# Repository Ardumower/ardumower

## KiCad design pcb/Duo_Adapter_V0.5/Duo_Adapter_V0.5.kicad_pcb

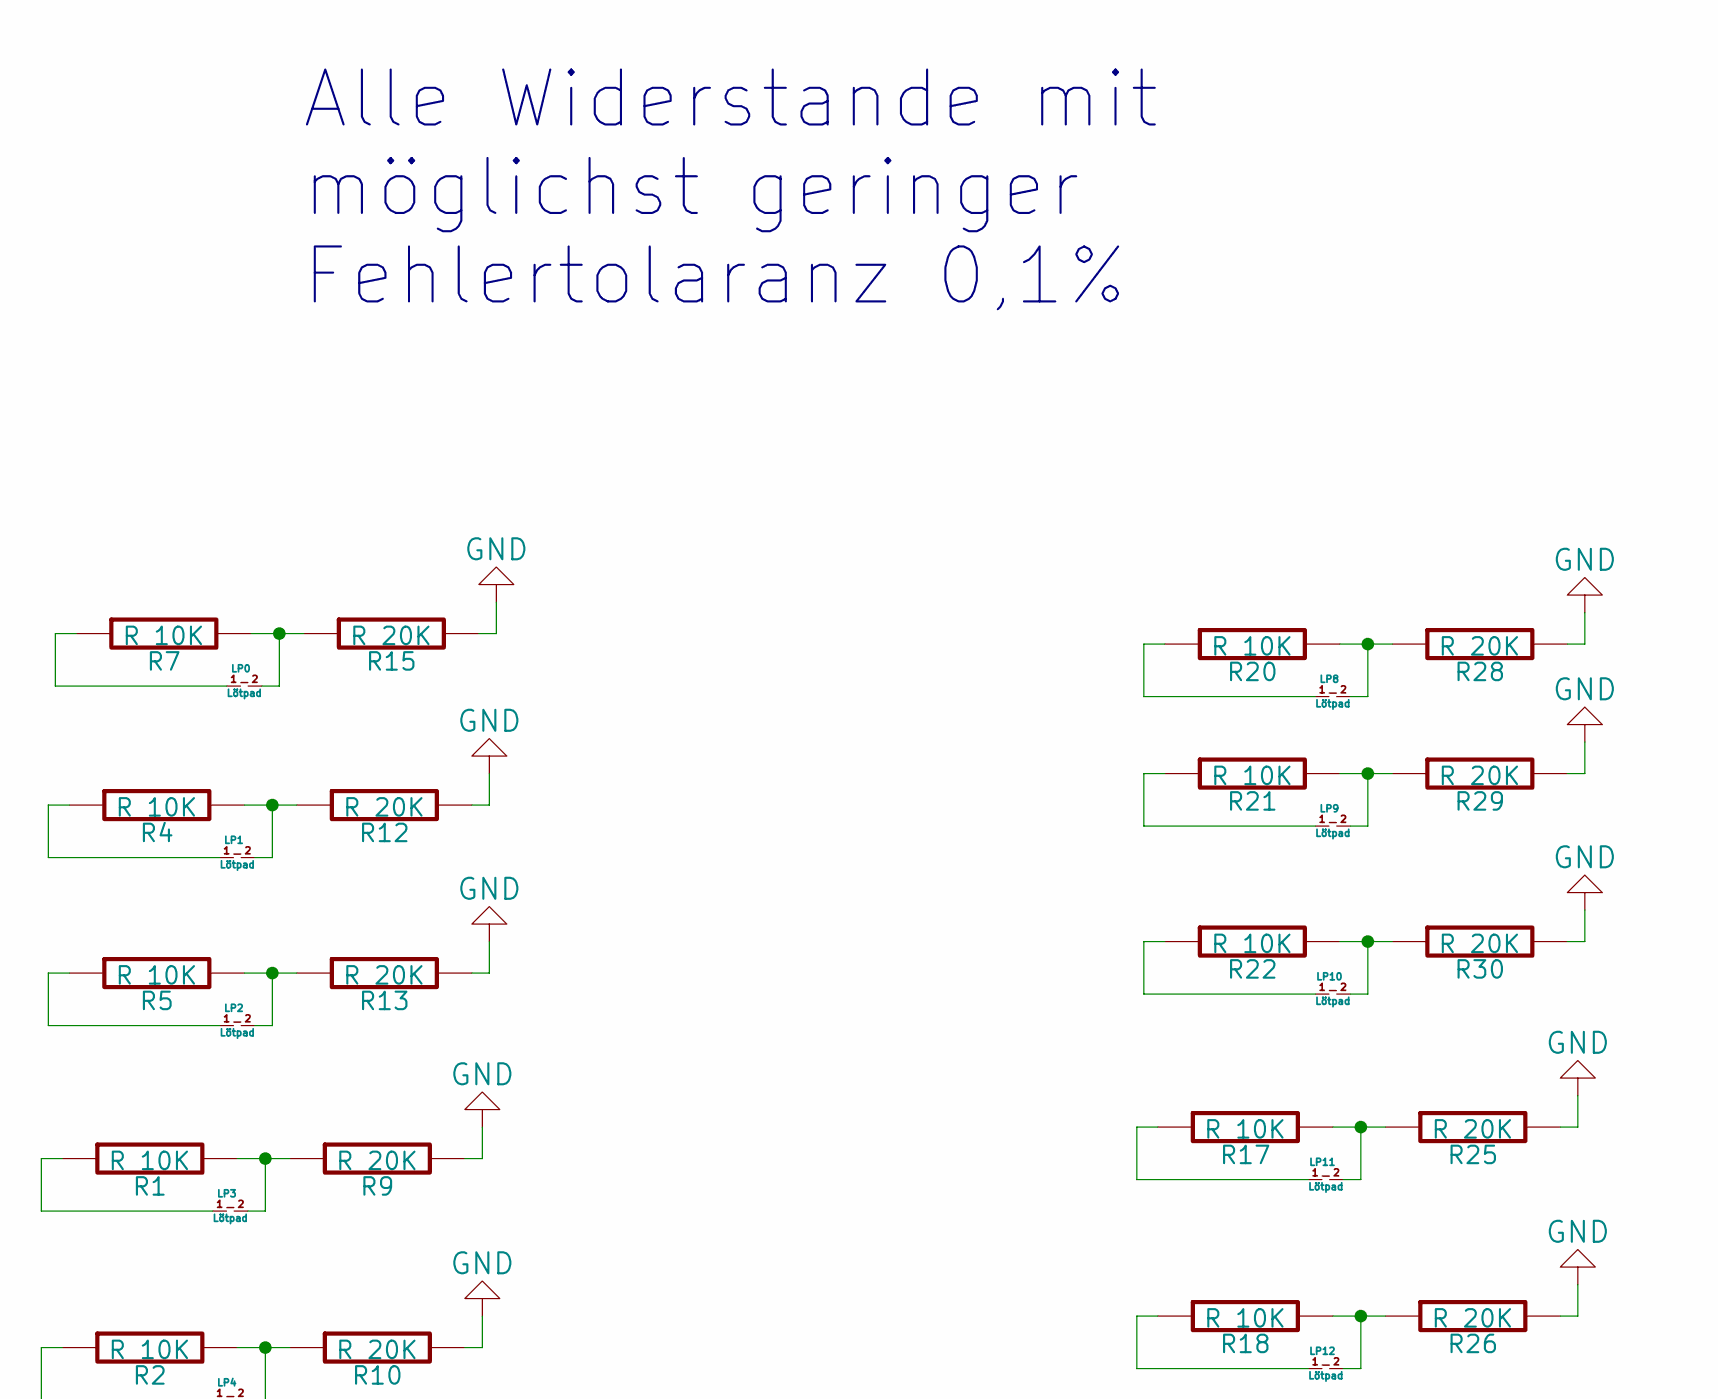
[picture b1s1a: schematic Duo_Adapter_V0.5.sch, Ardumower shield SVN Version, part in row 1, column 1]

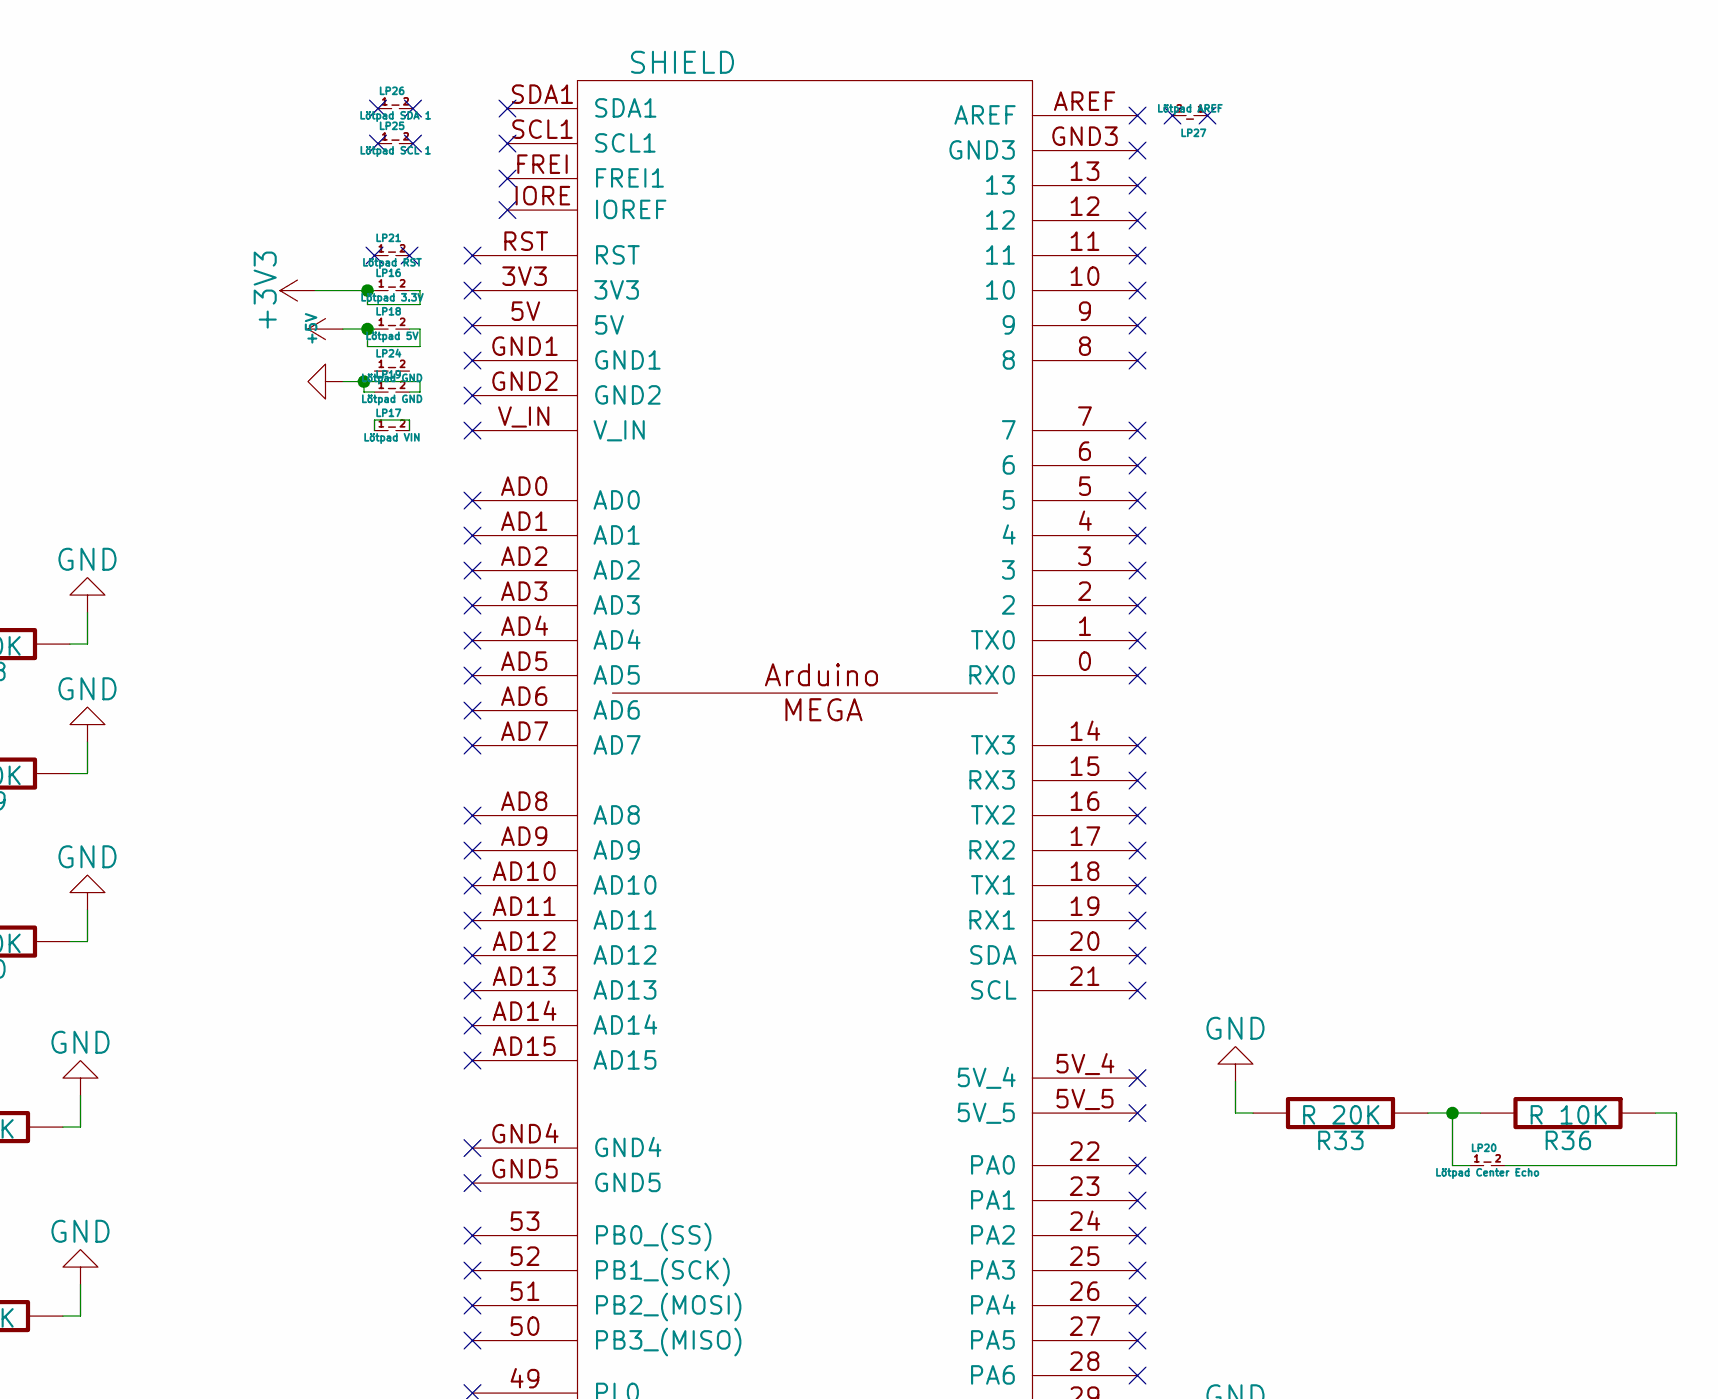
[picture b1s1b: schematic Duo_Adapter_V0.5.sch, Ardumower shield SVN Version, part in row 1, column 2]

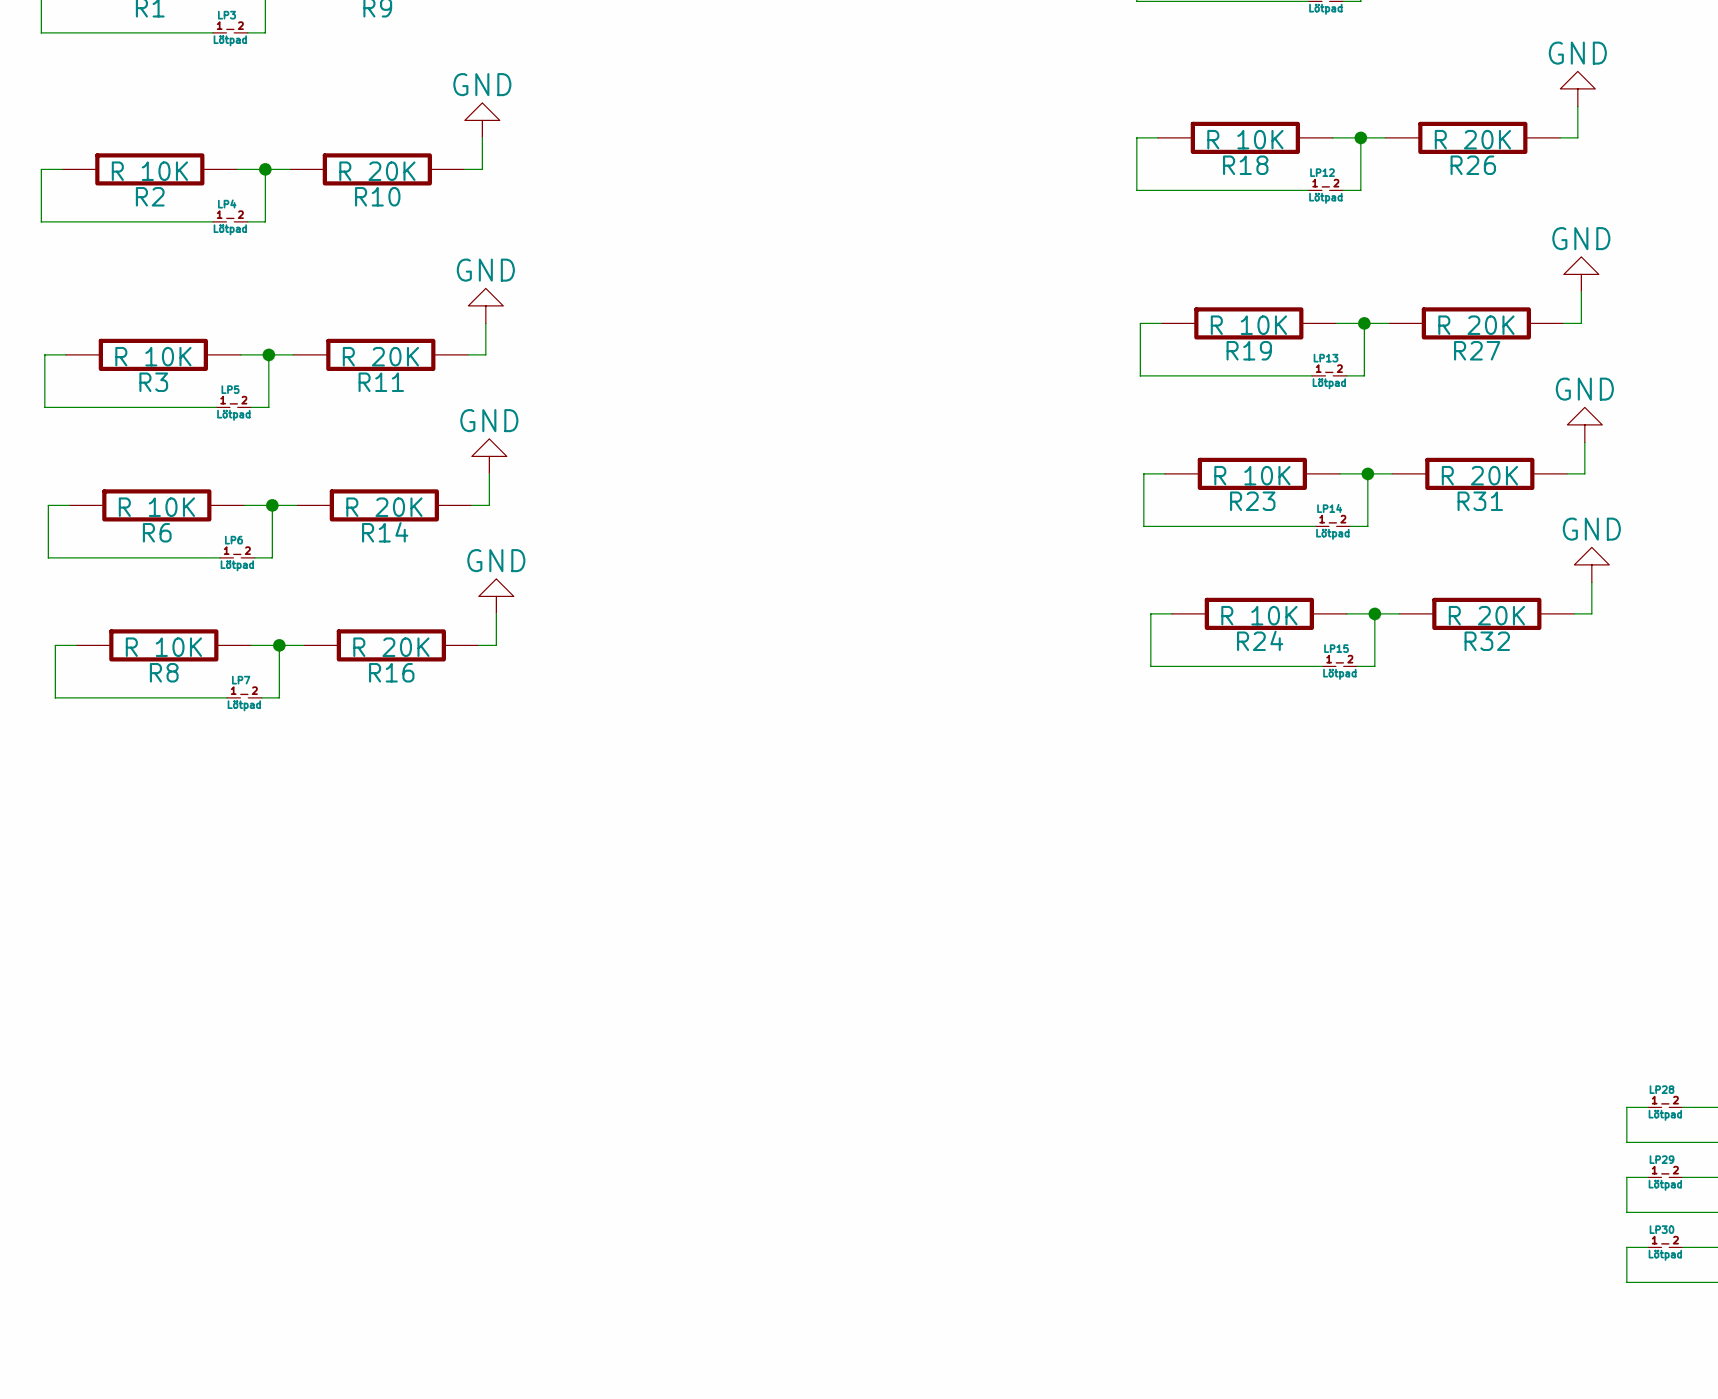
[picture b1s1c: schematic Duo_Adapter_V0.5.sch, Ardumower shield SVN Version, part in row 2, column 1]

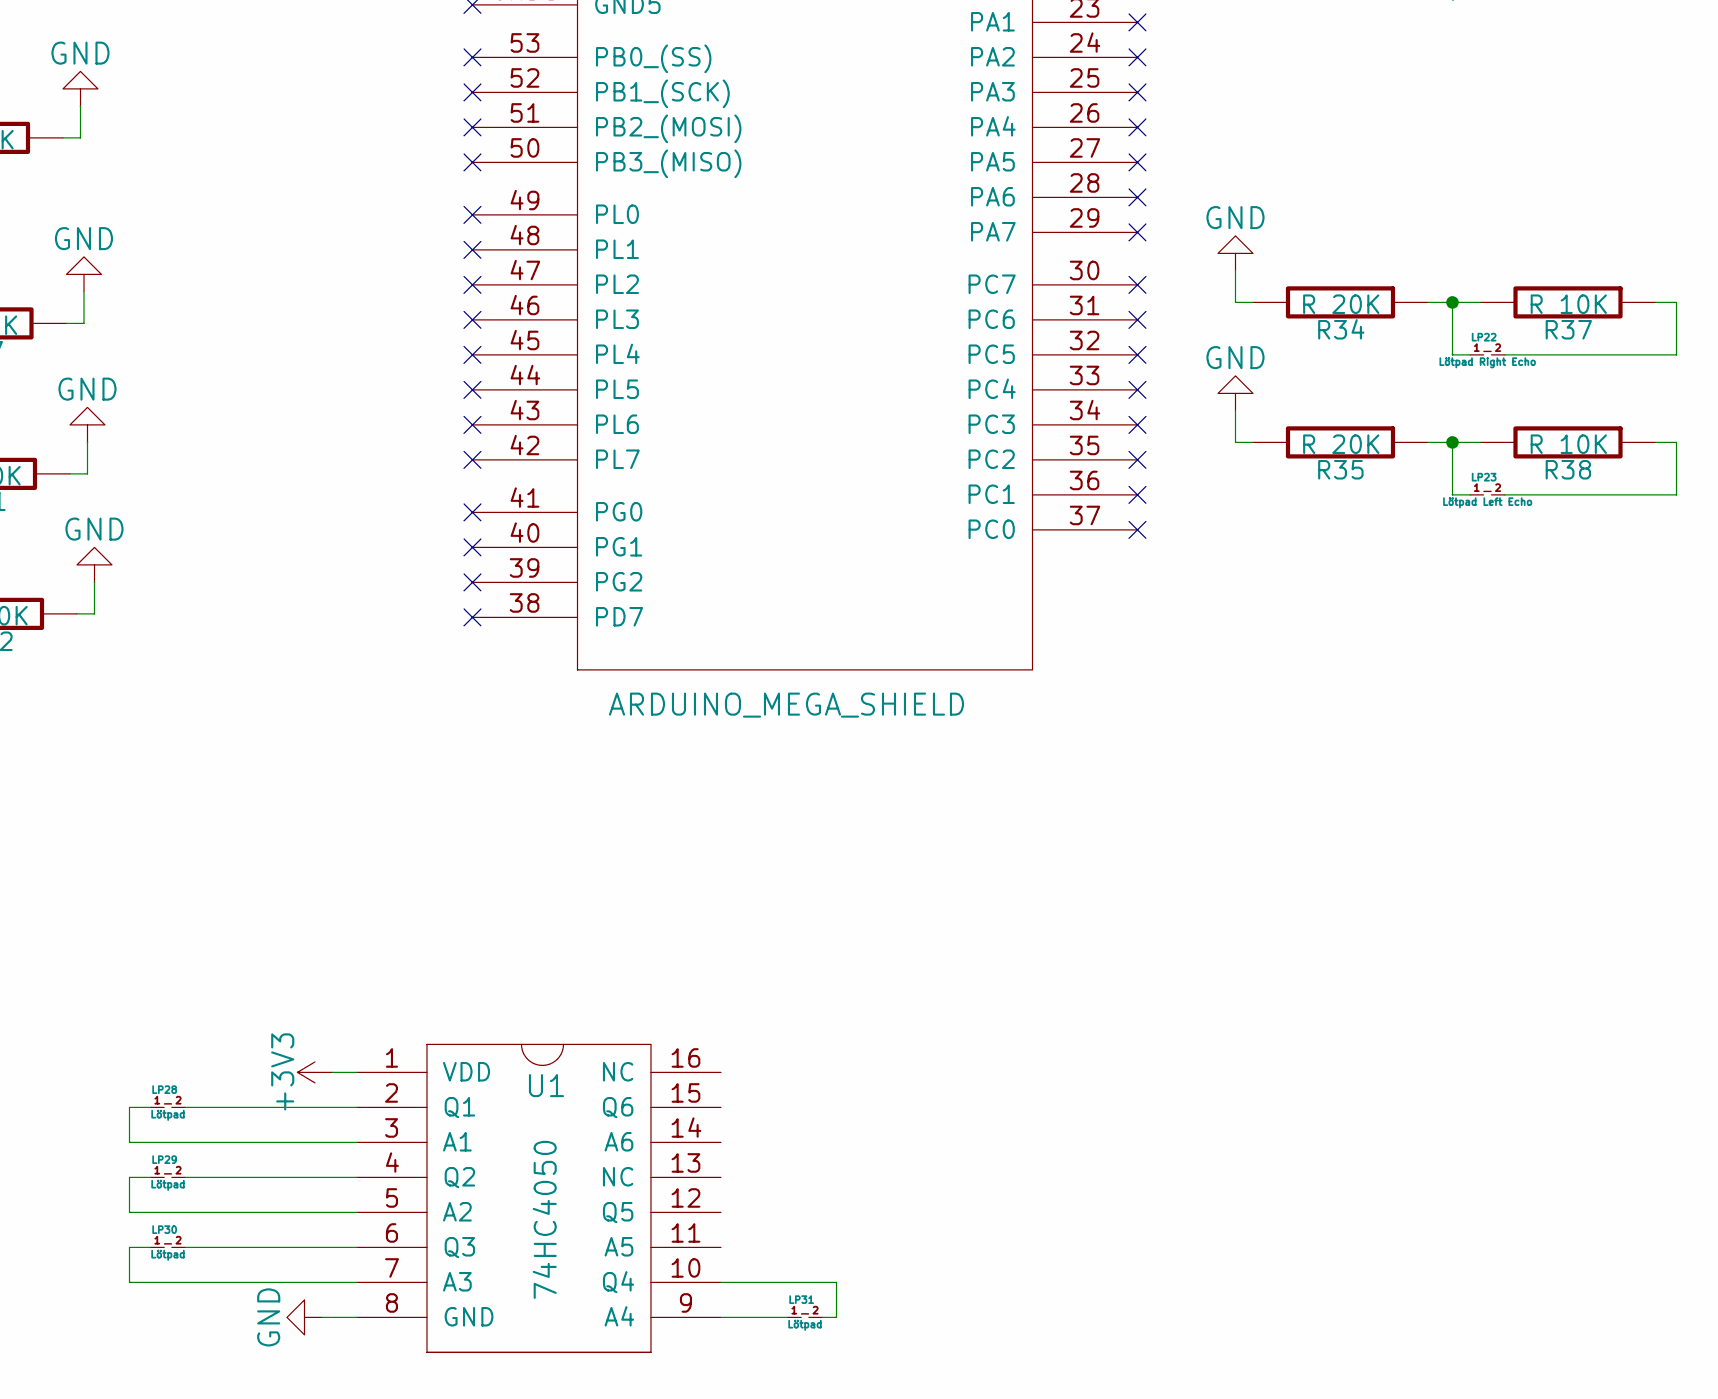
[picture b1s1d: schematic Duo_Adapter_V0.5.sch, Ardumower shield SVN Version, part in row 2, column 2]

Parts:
LP0, LP1, LP2, LP3, LP4, LP5, LP6, LP7, LP8, LP9, LP10, LP11, LP12, LP13, LP14, LP15, LP28, LP29, LP30, LP31: Lötpad; Lötpad_1x02_Buchse
LP16: Lötpad 3.3V; Lötpad_1x02_Buchse
LP17: Lötpad VIN; Lötpad_1x02_Buchse
LP18: Lötpad 5V; Lötpad_1x02_Buchse
LP19, LP24: Lötpad GND; Lötpad_1x02_Buchse
LP20: Lötpad Center Echo; Lötpad_1x02_Buchse
LP21: Lötpad RST; Lötpad_1x02_Buchse
LP22: Lötpad Right Echo; Lötpad_1x02_Buchse
LP23: Lötpad Left Echo; Lötpad_1x02_Buchse
LP25: Lötpad SCL 1; Lötpad_1x02_Buchse
LP26: Lötpad SDA 1; Lötpad_1x02_Buchse
LP27: Lötpad AREF; Lötpad_1x02_Buchse
R1, R2, R3, R4, R5, R6, R7, R8, R17, R18, R19, R20, R21, R22, R23, R24, R36, R37, R38: R 10K; Resistor_Horizontal_RM10mm
R9, R10, R11, R12, R13, R14, R15, R16, R25, R26, R27, R28, R29, R30, R31, R32, R33, R34, R35: R 20K; Resistor_Horizontal_RM10mm
SHIELD1: ARDUINO_MEGA_SHIELD; ARDUINO_MEGA_SHIELD_DUO_3D
U1: 74HC4050; DIP-16__300

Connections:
+3V3: LP16.1, LP16.2, U1.1 (VDD)
+5V: LP18.1, LP18.2
GND: LP19.1, LP19.2, R9.2, R10.2, R11.2, R12.2, R13.2, R14.2, R15.2, R16.2, R25.2, R26.2, R27.2, R28.2, R29.2, R30.2, R31.2, R32.2, R33.2, R34.2, R35.2, U1.8 (GND)
unnamed: LP0.1, R7.1
unnamed: LP0.2, R7.2, R15.1
unnamed: LP1.1, R4.1
unnamed: LP1.2, R4.2, R12.1
unnamed: LP2.1, R5.1
unnamed: LP2.2, R5.2, R13.1
unnamed: LP3.1, R1.1
unnamed: LP3.2, R1.2, R9.1
unnamed: LP4.1, R2.1
unnamed: LP4.2, R2.2, R10.1
unnamed: LP5.1, R3.1
unnamed: LP5.2, R3.2, R11.1
unnamed: LP6.1, R6.1
unnamed: LP6.2, R6.2, R14.1
unnamed: LP7.1, R8.1
unnamed: LP7.2, R8.2, R16.1
unnamed: LP8.1, R20.1
unnamed: LP8.2, R20.2, R28.1
unnamed: LP9.1, R21.1
unnamed: LP9.2, R21.2, R29.1
unnamed: LP10.1, R22.1
unnamed: LP10.2, R22.2, R30.1
unnamed: LP11.1, R17.1
unnamed: LP11.2, R17.2, R25.1
unnamed: LP12.1, R18.1
unnamed: LP12.2, R18.2, R26.1
unnamed: LP13.1, R19.1
unnamed: LP13.2, R19.2, R27.1
unnamed: LP14.1, R23.1
unnamed: LP14.2, R23.2, R31.1
unnamed: LP15.1, R24.1
unnamed: LP15.2, R24.2, R32.1
unnamed: LP17.1, LP17.2
unnamed: LP20.1, R33.1, R36.2
unnamed: LP20.2, R36.1
unnamed: LP22.1, R34.1, R37.2
unnamed: LP22.2, R37.1
unnamed: LP23.1, R35.1, R38.2
unnamed: LP23.2, R38.1
unnamed: LP28.1, U1.3 (A1)
unnamed: LP28.2, U1.2 (Q1)
unnamed: LP29.1, U1.5 (A2)
unnamed: LP29.2, U1.4 (Q2)
unnamed: LP30.1, U1.7 (A3)
unnamed: LP30.2, U1.6 (Q3)
unnamed: LP31.1, U1.9 (A4)
unnamed: LP31.2, U1.10 (Q4)

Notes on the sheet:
Alle Widerstande mit möglichst geringer Fehlertolaranz 0,1%

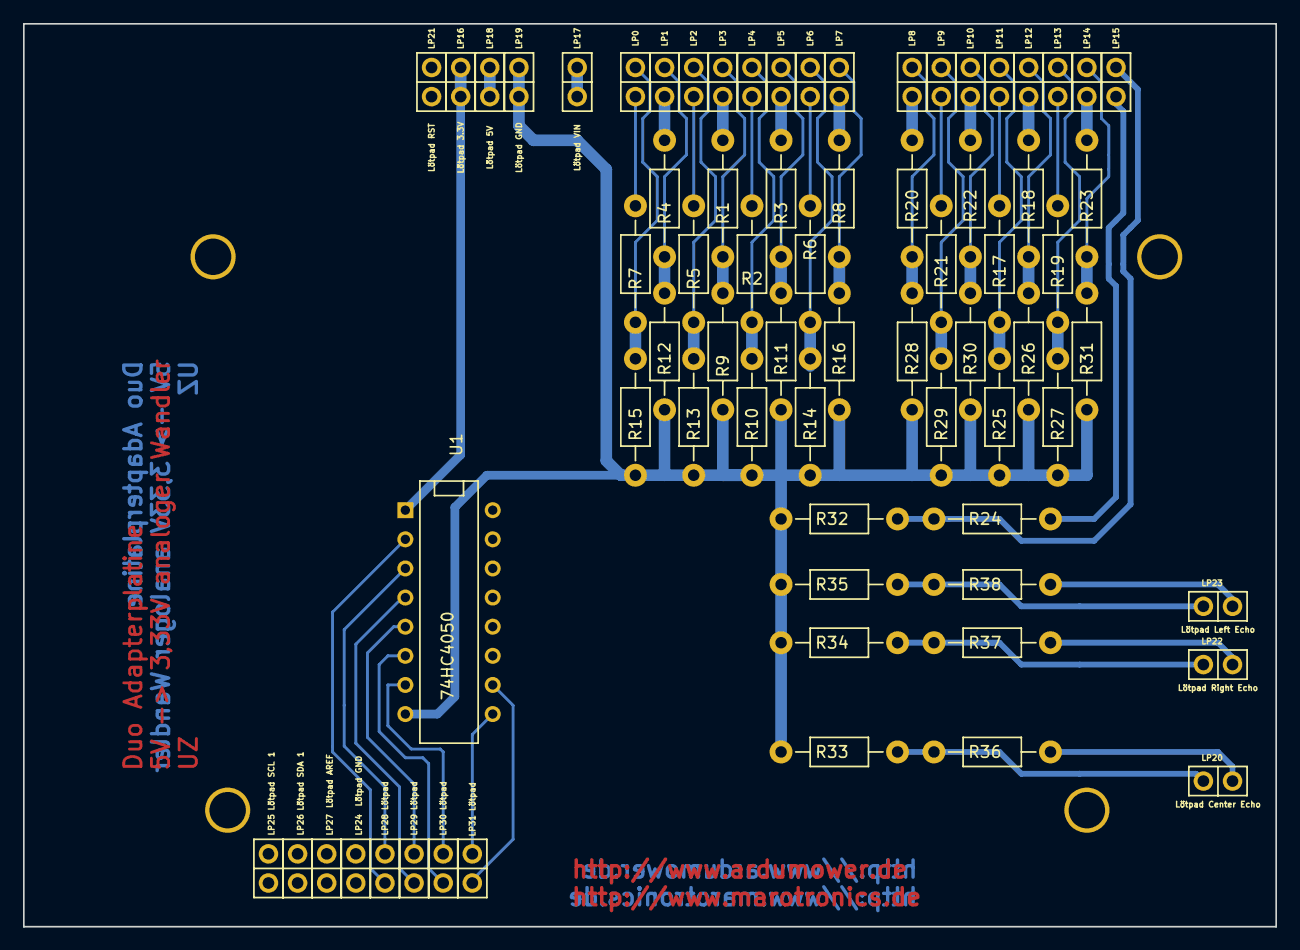
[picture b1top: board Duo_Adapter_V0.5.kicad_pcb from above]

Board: 2 copper layers, 109.2 x 78.7 mm, 72 parts (1 on the bottom side), 50 nets.

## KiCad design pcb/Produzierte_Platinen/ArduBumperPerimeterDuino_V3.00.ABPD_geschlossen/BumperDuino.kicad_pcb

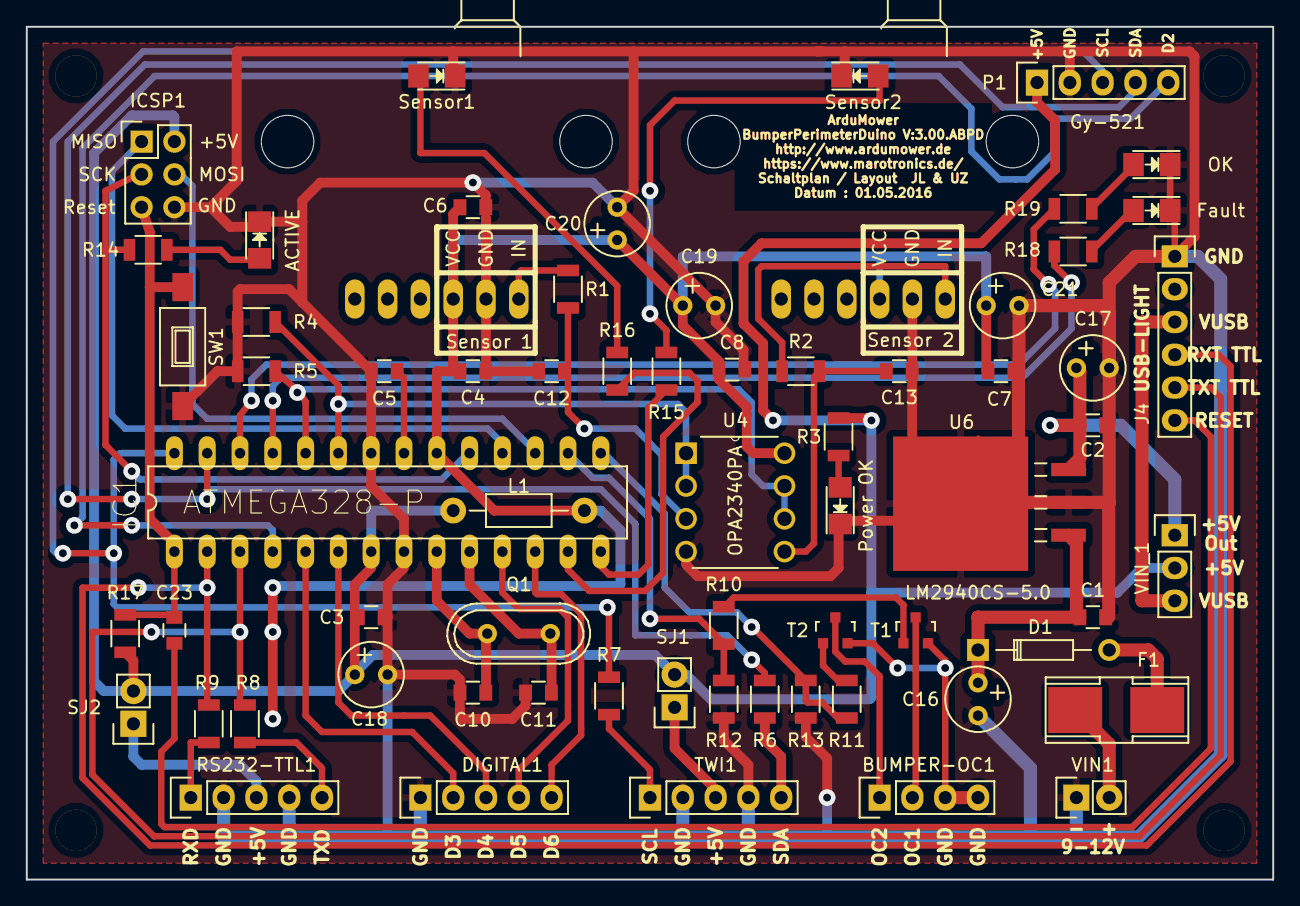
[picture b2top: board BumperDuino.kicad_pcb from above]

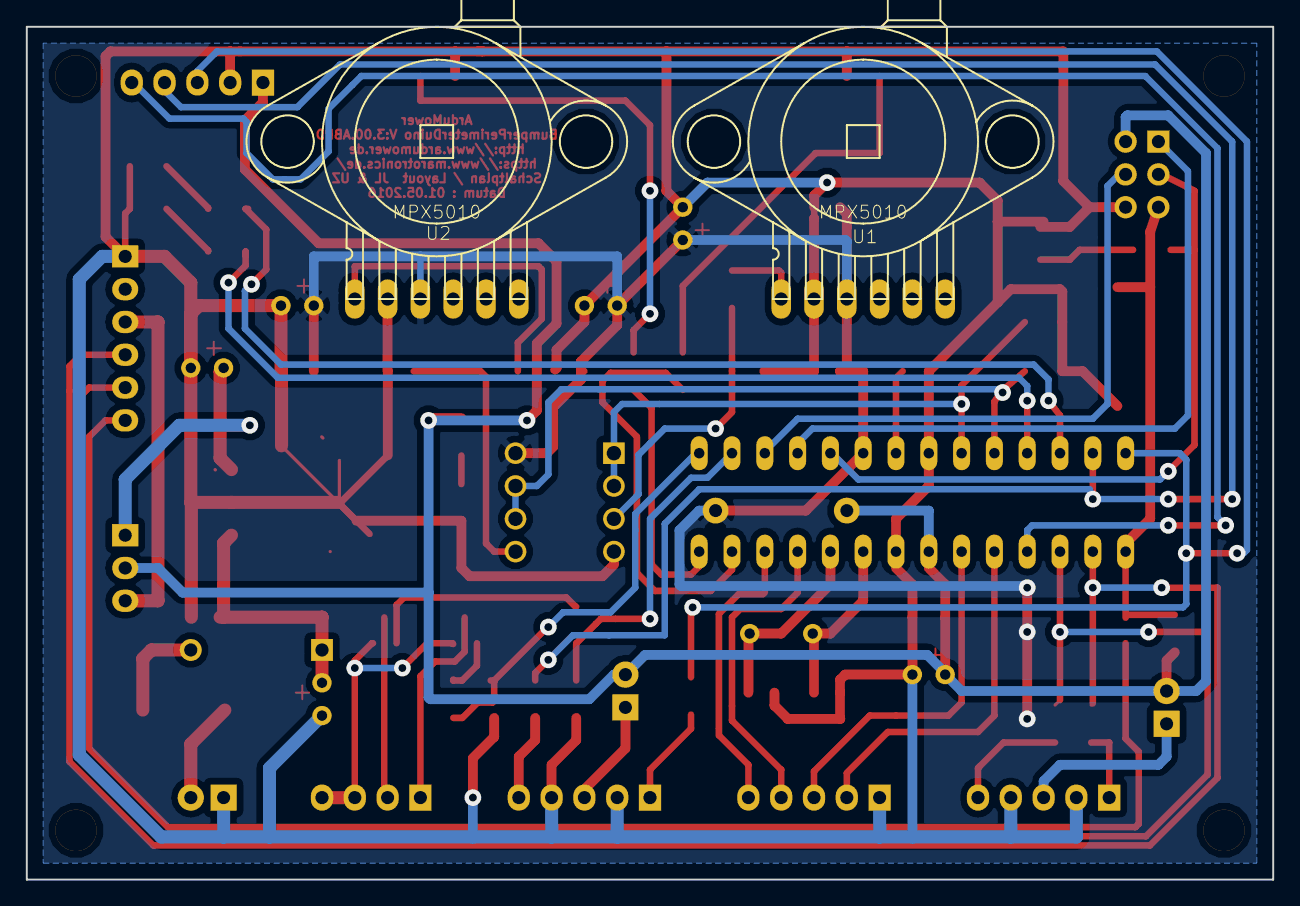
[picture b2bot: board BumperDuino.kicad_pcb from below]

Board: 2 copper layers, 96.5 x 66.0 mm, 71 parts (2 on the bottom side), 54 nets.

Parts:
ACTIVE1: ACTIVE; LED_1206
B1, B2, B3, B4: Bohrloch; Bohrloch_3,2mm
BUMPER-OC1: BUMPER-OC; Pin_Header_Straight_1x04
C1, C2, C3, C4, C5, C6, C7, C8, C23: 100nF; C_0805
C10, C11: 27pF; C_0805
C12, C13: 330nF; C_0805
C16, C18, C19, C20, C21: 10uF; Elko_vert_11x5mm_RM2.5
C17: 22uF; Elko_vert_11x5mm_RM2.5
D1: 1N4004; Diode_DO-35_SOD27_Horizontal_RM10
DIGITAL1: DIGITAL; Pin_Header_Straight_1x05
F1: PTC; Fuse_SMD
Fault1: Fault; LED_1206
IC1: ATMEGA328-P; atmega8-DIL28-3
ICSP1: ICSP; Pin_Header_Straight_2x03
J4: J4; Pin_Header_Straight_1x06
L1: 10uH; Resistor_Horizontal_RM10mm
OK1: OK; LED_1206
P1: Gy-521; Pin_Header_Straight_1x05
PowerOK1: Power OK; LED_1206
Q1: 16MHz; Crystal_HC49-U_Vertical
R1, R2: 680; R_1206
R3, R14, R15, R16, R17, R18, R19: 1K; R_1206
R4, R5, R12, R13: 10K; R_1206
R6, R7, R8, R9: 100; R_1206
R10, R11: 2K7; R_1206
RS232-TTL1: RS232-TTL; Pin_Header_Straight_1x05
SJ1, SJ2: Jumper_NC_Small; Pin_Header_Straight_1x02
SW1: Reset; SW_SPST_FSMSM
Sensor1: Sensor 1; LED_1206
Sensor2: Sensor 2; LED_1206
T1, T2: BC847B; SOT-23
TWI1: TWI; Pin_Header_Straight_1x05
U1, U2: MPX5010; 867C-H
U4: OPA2340PA; DIP254P762X508-8
U6: LM2940CS-5.0; TO254P1435X464-4N
VIN1: VIN; Pin_Header_Straight_1x02
VIN_1: VIN_; Pin_Header_Straight_1x03

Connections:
+5V: C3.2, C18.1, IC1.7, ICSP1.2, L1.1, P1.1, R3.2, R17.2, SJ1.2, SJ2.2, VIN_1.2
ADC0: IC1.23, R4.2, U4.1, U4.2
ADC1: IC1.24, R5.2, U4.6, U4.7
BUMPER-OC1: IC1.15, R11.2, R13.1
BUMPER-OC2: IC1.16, R10.2, R12.1
D2: IC1.4, P1.5
D3: DIGITAL1.2, IC1.5
D4: DIGITAL1.3, IC1.6
D5: DIGITAL1.4, IC1.11
D6: DIGITAL1.5, IC1.12
GND: ACTIVE1.1, C1.2, C2.2, C3.1, C4.2, C5.2, C6.2, C7.2, C8.2, C10.2, C11.2, C12.2, C13.2, C16.2, C17.2, C18.2, C19.2, C20.2, C21.2, DIGITAL1.1, Fault1.1, IC1.8, IC1.22, ICSP1.6, J4.1, OK1.1, P1.2, PowerOK1.1, R4.1, R5.1, R12.2, R13.2, RS232-TTL1.2, RS232-TTL1.4, SW1.2, Sensor1.1, Sensor2.1, TWI1.2, TWI1.4, U1.2, U2.2, U4.4, U6.2, U6.4, VIN1.1
LED-COL1: IC1.13, R16.2
LED-COL2: IC1.14, R15.2
LED-CRASH: IC1.25, R18.2
LED-INIT-OK: IC1.26, R19.2
MISO: IC1.18, ICSP1.1
MOSI: IC1.17, ICSP1.4
unnamed: ACTIVE1.2, R14.1
unnamed: BUMPER-OC1.1, T2.3
unnamed: BUMPER-OC1.2, T1.3
unnamed: BUMPER-OC1.3, BUMPER-OC1.4, T1.2, T2.2
unnamed: C1.1, C16.1, D1.1, U6.1
unnamed: C5.1, IC1.21
unnamed: C10.1, IC1.9, Q1.2
unnamed: C11.1, IC1.10, Q1.1
unnamed: C12.1, R1.2, U4.3
unnamed: C13.1, R2.2, U4.5
unnamed: C2.1, C17.1, U6.3, VIN_1.1
unnamed: C23.1, J4.6
unnamed: D1.2, F1.2
unnamed: F1.1, VIN1.2
unnamed: Fault1.2, R18.1
unnamed: OK1.2, R19.1
unnamed: PowerOK1.2, R3.1
unnamed: R1.1, U1.1
unnamed: R2.1, U2.1
unnamed: R6.2, TWI1.5
unnamed: R7.2, TWI1.1
unnamed: R8.2, RS232-TTL1.5
unnamed: R9.2, RS232-TTL1.1
unnamed: R10.1, T1.1
unnamed: R11.1, T2.1
unnamed: R15.1, Sensor2.2
unnamed: R16.1, Sensor1.2
unnamed: RS232-TTL1.3, SJ2.1
unnamed: SJ1.1, TWI1.3
RXD_TTL: IC1.2, J4.4, R9.1
Reset: C23.2, IC1.1, ICSP1.5, R17.1, SW1.1
SCK: IC1.19, ICSP1.3, R14.2
SCL: IC1.28, P1.3, R7.1
SDA: IC1.27, P1.4, R6.1
TXD_TTL: IC1.3, J4.5, R8.1
VCC: C4.1, C6.1, C7.1, C8.1, C19.1, C20.1, C21.1, IC1.20, L1.2, U1.3, U2.3, U4.8
VUSB: J4.3, VIN_1.3

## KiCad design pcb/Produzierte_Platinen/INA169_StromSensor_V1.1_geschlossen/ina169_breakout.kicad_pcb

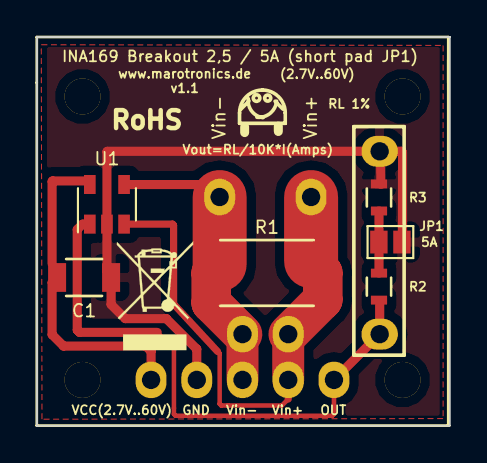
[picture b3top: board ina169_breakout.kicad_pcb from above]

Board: 2 copper layers, 22.9 x 21.6 mm, 8 parts (0 on the bottom side), 6 nets.

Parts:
C1: 0.1uF; C_1206
H1: Mülleimer; WEEE-Logo_4.2x6mm_SilkScreen
J1: INA169 Breakout 2,5 / 5A (short pad JP1); ina169_breakout_footprint_mit_unterem_Lötpad
JP1: 5A; GS2
R1: 0.1 1% 2W; R_2512
R2, R3: 10K 1%; R_0603
U1: INA169_IC; SOT-23-5

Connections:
/Out: J1.5, R2.1, U1.1
/VCC: C1.1, J1.1, U1.5
/Vin+: J1.4, R1.1, U1.3
/Vin-: J1.3, R1.2, U1.4
GND: C1.2, J1.2, JP1.2, R3.2, U1.2
unnamed: JP1.1, R2.2, R3.1

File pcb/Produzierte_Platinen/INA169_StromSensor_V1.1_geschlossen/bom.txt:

C1  0.1uF  1206   SMD 12 X7R-G1206 100N        
R1  0.1  1%  2W   2512  SMD CRM2512-FX-R100ELF  
R2,R3   10K  1%   0603  
U1   INA169 SOT23-5

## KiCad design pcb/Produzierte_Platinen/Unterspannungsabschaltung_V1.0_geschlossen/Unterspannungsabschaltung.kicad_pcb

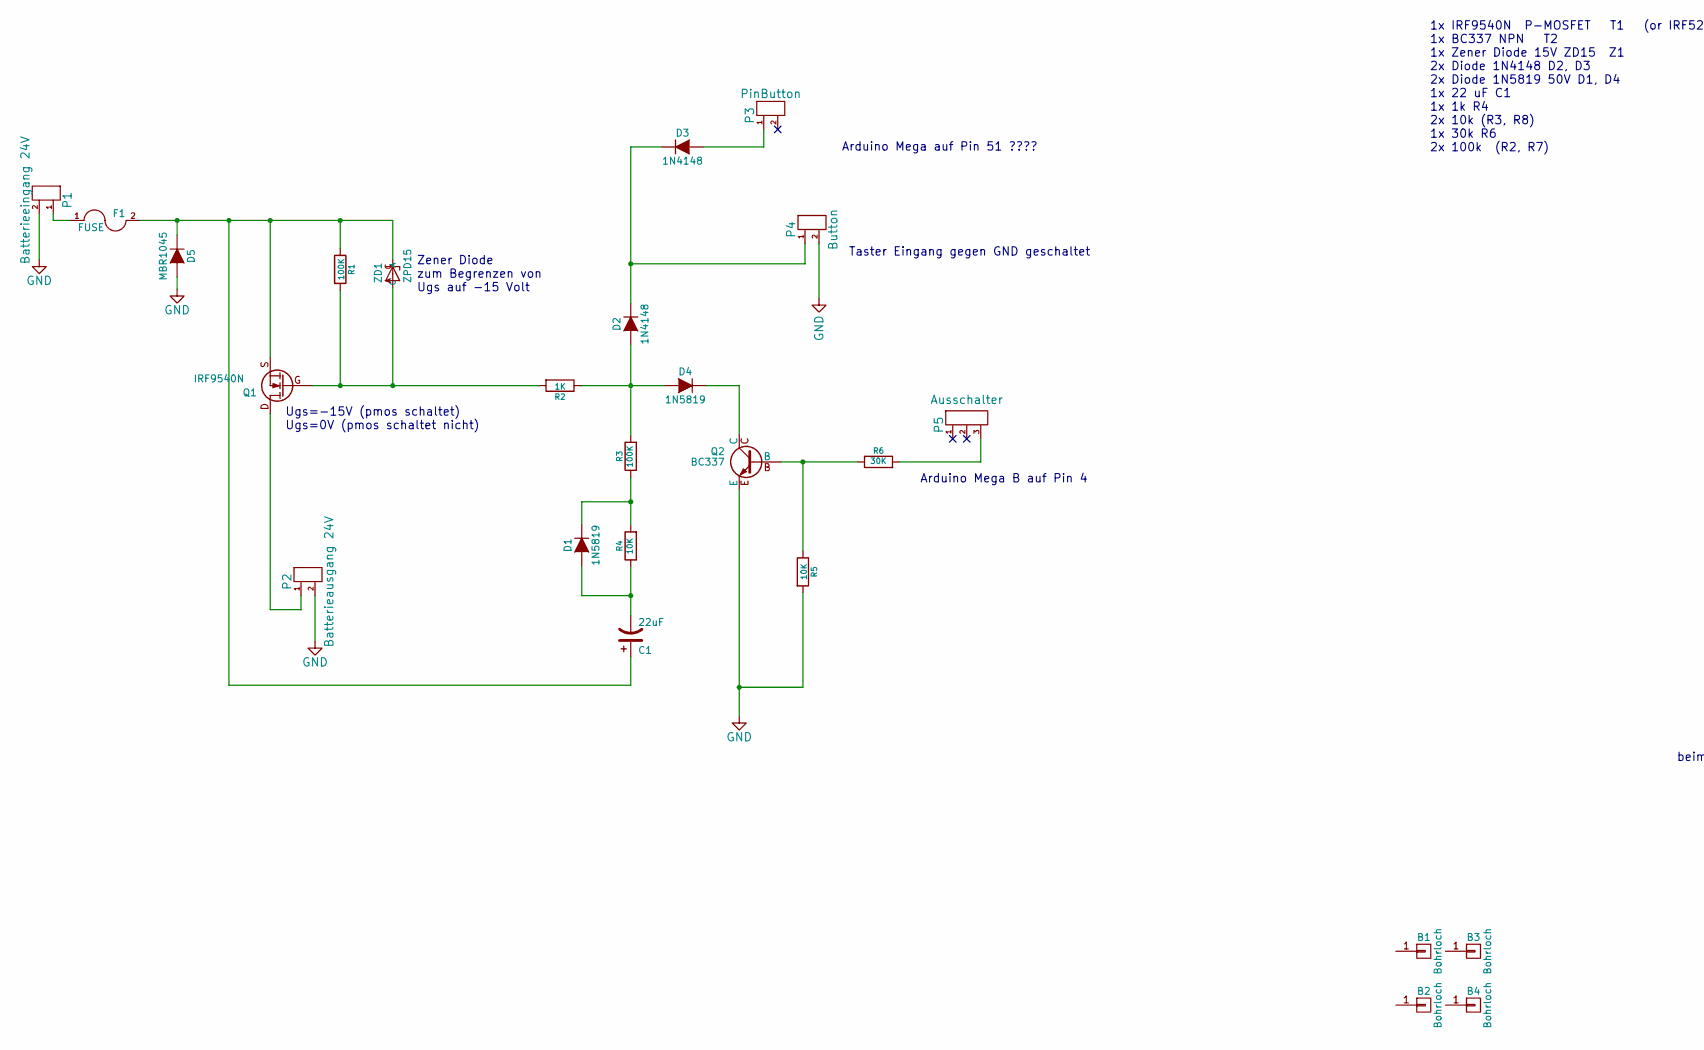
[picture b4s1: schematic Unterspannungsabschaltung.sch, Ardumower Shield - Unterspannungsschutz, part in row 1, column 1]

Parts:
B1, B2, B3, B4: Bohrloch; Bohrloch_3,2mm
C1: 22uF; Elko_vert_11.2x6.3mm_RM2.5_RM5.0
D1, D4: 1N5819; Diode_ligend_RM10
D2, D3: 1N4148; Diode_ligend_RM10
D5: MBR1045
F1: FUSE; Fuseholder_Reichelt_PL112000
P1: Batterieeingang 24V; Anschlussklemme_RM5,08-RM7,62
P2: Batterieausgang 24V; Anschlussklemme_RM5,08-RM7,62
P3: PinButton; Pin_Header_Straight_1x02
P4: Button; Pin_Header_Straight_1x02
P5: Ausschalter; Pin_Header_Straight_1x03
Q1: IRF9540N; TO-220_FET-GDS_Vertical
Q2: BC337; TO92-EBC
R1, R3: 100K; Resistor_Horizontal_RM10mm
R2: 1K; Resistor_Horizontal_RM10mm
R4, R5: 10K; Resistor_Horizontal_RM10mm
R6: 30K; Resistor_Horizontal_RM10mm
ZD1: ZPD15; Diode_ligend_RM10

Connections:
GND: D5.2 (A), P1.2, P2.2, P4.2, Q2.E, R5.2
unnamed: C1.1, D5.1 (K), F1.2, Q1.S, R1.1, ZD1.C
unnamed: C1.2, D1.2 (A), R4.1
unnamed: D1.1 (K), R3.1, R4.2
unnamed: D2.1 (K), D3.1 (K), P4.1
unnamed: D2.2 (A), D4.2 (A), R2.1, R3.2
unnamed: D3.2 (A), P3.1
unnamed: D4.1 (K), Q2.C
unnamed: F1.1, P1.1
unnamed: P2.1, Q1.D
unnamed: P5.3, R6.2
unnamed: Q1.G, R1.2, R2.2, ZD1.A
unnamed: Q2.B, R5.1, R6.1

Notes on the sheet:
Taster Eingang gegen GND geschaltet
Arduino Mega auf Pin 51 ????
Arduino Mega B auf Pin 4
1x IRF9540N P-MOSFET T1 (or IRF5210) 1x BC337 NPN T2 1x Zener Diode 15V ZD15 Z1 2x Diode 1N4148 D2, D3 2x Diode 1N5819 50V D1, D4 1x 22 uF C1 1x 1k R4 2x 10k (R3, R8) 1x 30k R6 2x 100k (R2, R7)
vielleicht schreibst du noch bei was die teilschaltungen machen sollen [00:05:52] Alexander Grau: zener diode z.b. soll Ugs auf -15 volt begrenzen [00:06:31] Alexander Grau: C9 und D13 sollen über R31, R30 eine verzögerungsschaltung bilden [00:06:39] Alexander Grau: (für eine richtung) [00:07:27] A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
beim flashen über usb wird der akku getrennt (alle pins gehen auf hochomig) - das sollte aber kein problem sein (usb versorgung des arduinos) - beim programmstart wird der akku dann wieder zugeschaltet
Zener Diode zum Begrenzen von Ugs auf -15 Volt
Ugs=-15V (pmos schaltet) Ugs=0V (pmos schaltet nicht)

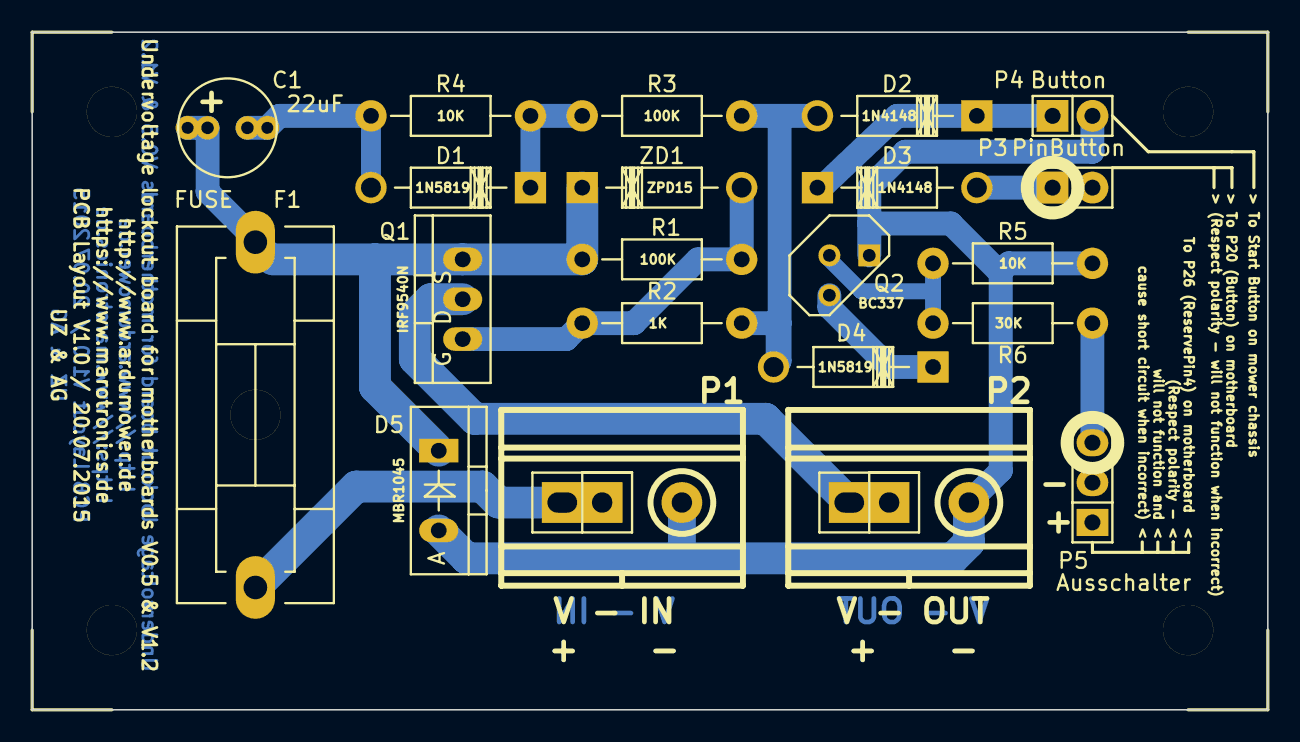
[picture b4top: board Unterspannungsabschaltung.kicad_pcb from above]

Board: 2 copper layers, 78.7 x 43.2 mm, 25 parts (0 on the bottom side), 13 nets.
